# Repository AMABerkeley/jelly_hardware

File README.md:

# jelly_hardware
Hardware for Jelly Robot

More to come...

Useful for protecting against sparks and having an isolated ground for a computer.

Input Voltage is 24V from this device: [Kobalt](https://www.lowes.com/pd/Kobalt-24-Volt-1-5-Amp-Hours-Lithium-Power-Tool-Battery/1000090833)

Output Voltage at XT30 and XT60 is 24V

Output Voltage at Isolated pins: 5V 5A

V1.0 has been sent out.

TODO V2.0: Add PMOS to 24V to prevent damage to circuit if battery connected wrong way. Add connector for computer power. Add LED indicators.

Components:

DCDC Isolated 5V5A
https://www.digikey.com/product-detail/en/traco-power/THL-25-2411/1951-1620-ND/9382657
https://www.tracopower.com/products/thl25.pdf
https://assets.tracopower.com/20190412132953/THL25/documents/thl25-application.pdf

Inductor
https://www.mouser.com/ProductDetail/Coilcraft/XEL6060-222MEB?qs=sGAEpiMZZMsg%252By3WlYCkU1c2wN3ttFq7viHBlk82CxY%3D

NMOS
current nmos https://www.digikey.com/product-detail/en/stmicroelectronics/STP160N3LL/497-16021-5-ND/5455754
backup NMOS https://www.digikey.com/product-detail/en/infineon-technologies/IRLB3813PBF/IRLB3813PBF-ND/2118485

Batttery Terminal Connector
https://www.digikey.com/product-detail/en/te-connectivity-amp-connectors/1-725996-2/A130982-ND/2055902
Specs https://www.te.com/commerce/DocumentDelivery/DDEController?Action=showdoc&DocId=Catalog+Section%7F82004_FASTON_PCB_Tabs_Receptacles%7F0914%7Fpdf%7FEnglish%7FENG_CS_82004_FASTON_PCB_Tabs_Receptacles_0914.pdf%7F725996-2

Inspiration: https://easyeda.com/editor#id=83191bc7c7a1436bab31f7c8314d08c5|0a66ceef99064df6ad66a18129efbc26

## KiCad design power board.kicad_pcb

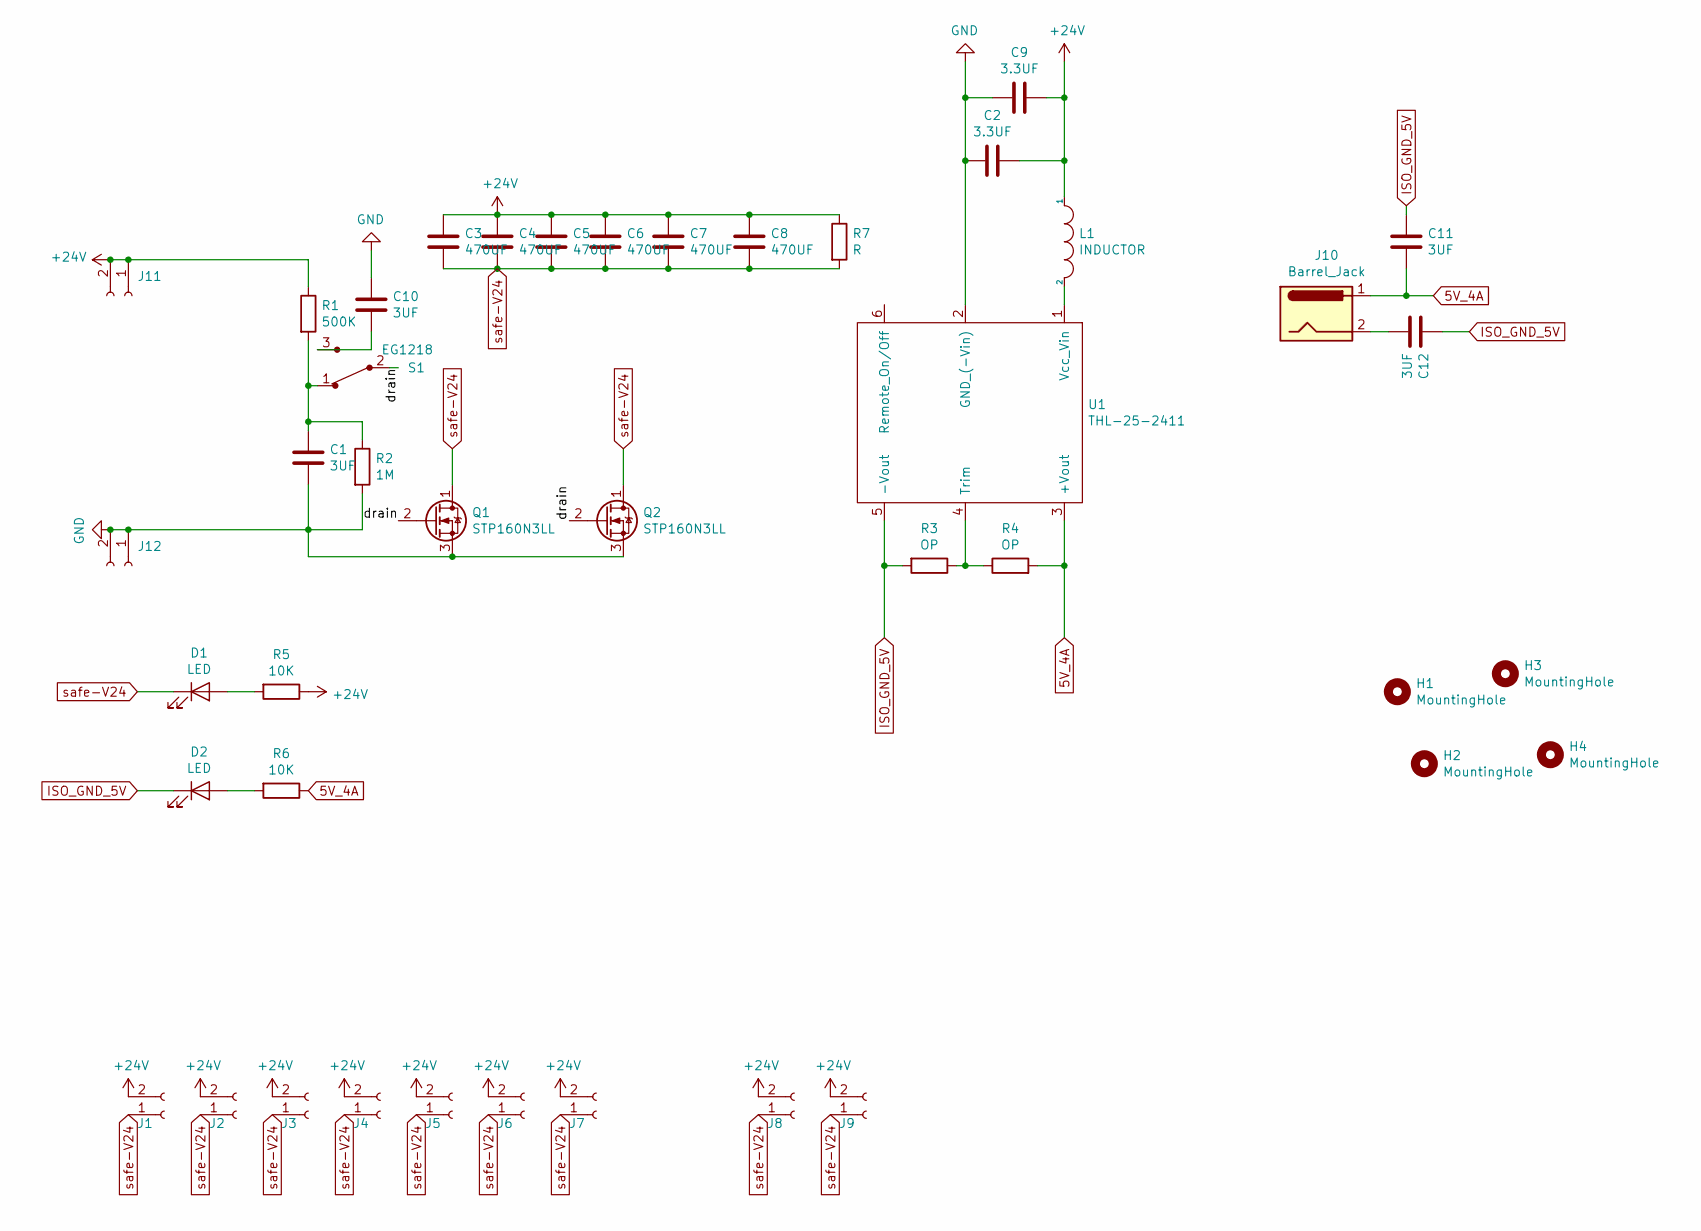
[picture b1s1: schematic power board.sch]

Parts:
C1, C10, C11, C12: 3UF; C_0805_2012Metric_Pad1.15x1.40mm_HandSolder
C2, C9: 3.3UF; C_0805_2012Metric_Pad1.15x1.40mm_HandSolder
C3, C4, C5, C6, C7, C8: 470UF; CP_Radial_D10.0mm_P5.00mm
D1, D2: LED; LED_0603_1608Metric_Pad1.05x0.95mm_HandSolder
H1, H2, H3, H4: MountingHole; MountingHole_3.2mm_M3_Pad_Via
J1, J2, J3, J4, J5, J6, J7: Conn_01x02_Female; AMASS_XT30U-F_1x02_P5.0mm_Vertical
J8, J9: Conn_01x02_Female; XT-60_female
J10: Barrel_Jack; BarrelJack_CUI_PJ-063AH_Horizontal
J11, J12: Conn_01x02_Female; battery_conector_powerpack
L1: INDUCTOR; XEL6060-152MEC
Q1, Q2: STP160N3LL; MOSFET_Down
R1: 500K; R_0805_2012Metric_Pad1.15x1.40mm_HandSolder
R2: 1M; R_0805_2012Metric_Pad1.15x1.40mm_HandSolder
R3, R4: OP; R_0805_2012Metric_Pad1.15x1.40mm_HandSolder
R5, R6: 10K; R_0805_2012Metric_Pad1.15x1.40mm_HandSolder
R7: R; R_0805_2012Metric_Pad1.15x1.40mm_HandSolder
S1: EG1218; Switch_Slide_11.6x4mm_EG1218; MPN EG1218; Digi-Key_PN EG1903-ND
U1: THL-25-2411; Converter_DCDC_TRACO_TEN20-xxxx_THT-modified

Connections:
5V_4A: C11.2, J10.1, R4.2, R6.1, U1.3 (+Vout)
+24V: C2.2, C3.1, C4.1, C5.1, C6.1, C7.1, C8.1, C9.2, J1.2, J2.2, J3.2, J4.2, J5.2, J6.2, J7.2, J8.2, J9.2, J11.1, J11.2, L1.1, R1.1, R5.1, R7.1
/drain: Q1.2 (G), Q2.2 (G), S1.2
GND: C1.2, C2.1, C9.1, C10.1, J12.1, J12.2, Q1.3 (S), Q2.3 (S), R2.2, U1.2 (GND_(-Vin))
ISO_GND_5V: C11.1, C12.1, D2.1 (K), R3.2, U1.5 (-Vout)
unnamed: C1.1, R1.2, R2.1, S1.1
unnamed: C10.2, S1.3
unnamed: C12.2, J10.2
unnamed: D1.2 (A), R5.2
unnamed: D2.2 (A), R6.2
unnamed: L1.2, U1.1 (Vcc_Vin)
unnamed: R3.1, R4.1, U1.4 (Trim)
safe-V24: C3.2, C4.2, C5.2, C6.2, C7.2, C8.2, D1.1 (K), J1.1, J2.1, J3.1, J4.1, J5.1, J6.1, J7.1, J8.1, J9.1, Q1.1 (D), Q2.1 (D), R7.2

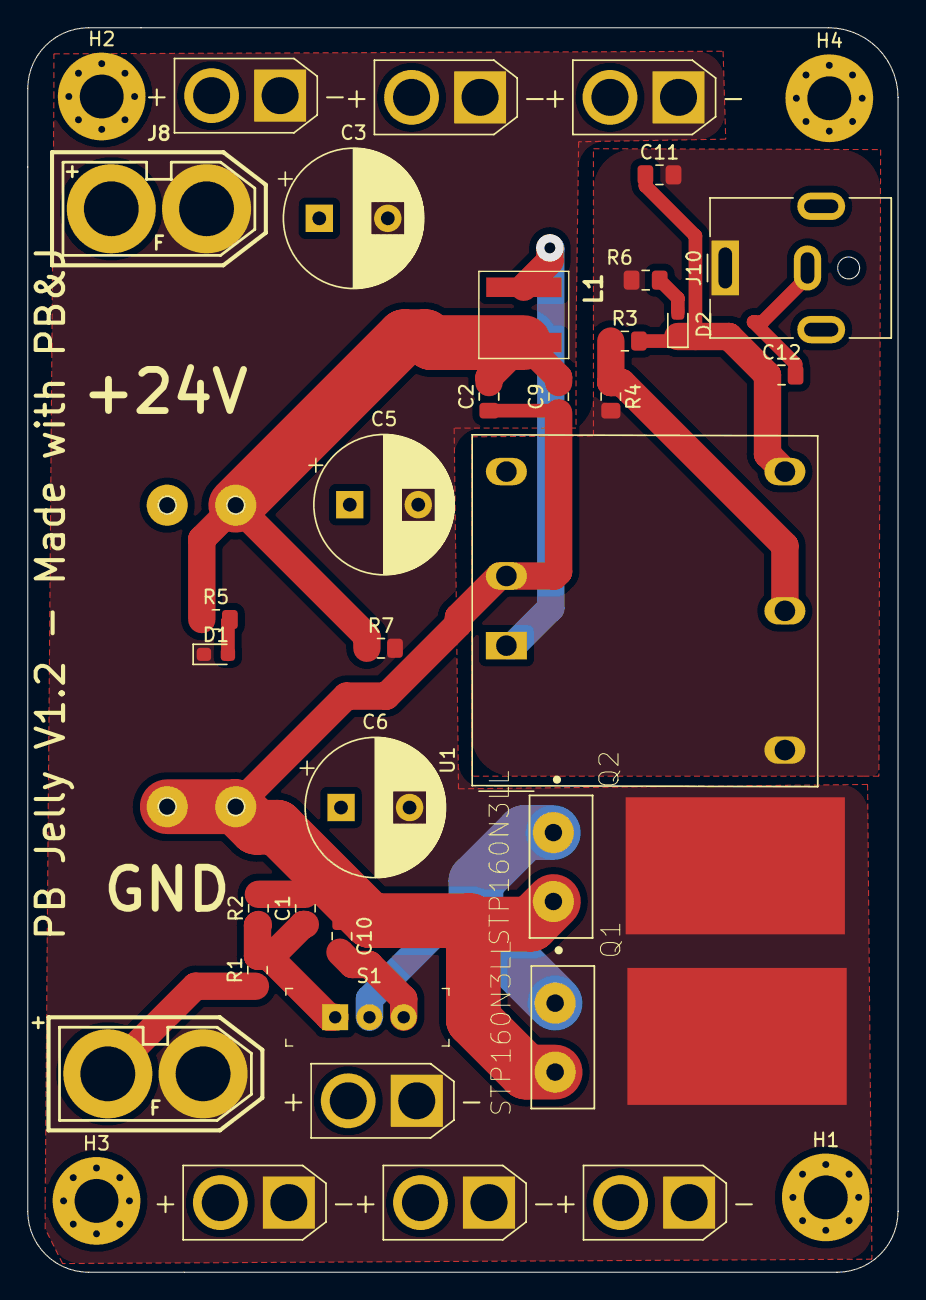
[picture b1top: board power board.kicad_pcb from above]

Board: 2 copper layers, 63.5 x 90.8 mm, 39 parts (0 on the bottom side), 13 nets.

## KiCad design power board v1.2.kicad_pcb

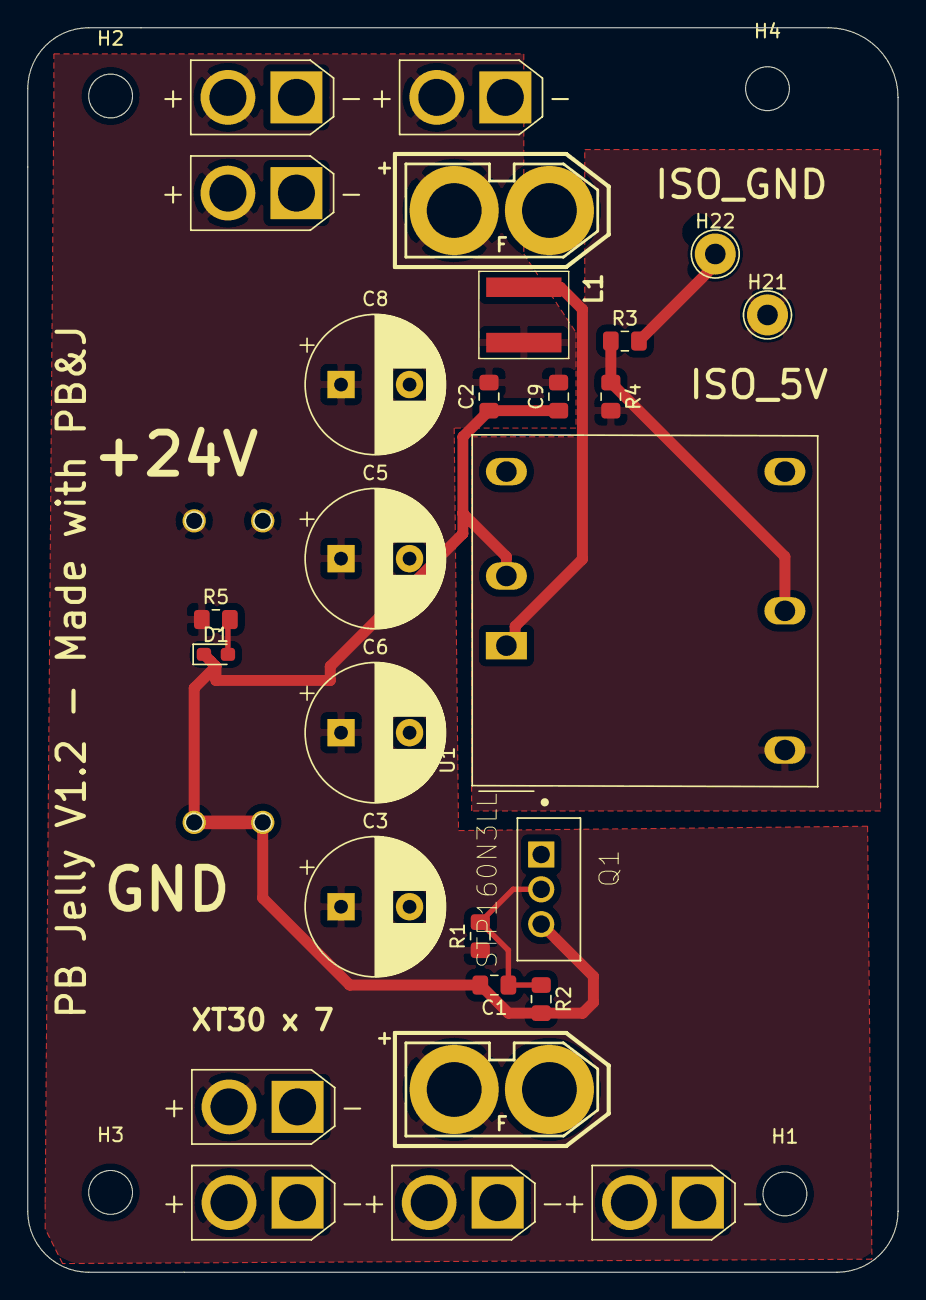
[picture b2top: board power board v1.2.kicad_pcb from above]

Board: 2 copper layers, 63.5 x 90.8 mm, 33 parts (0 on the bottom side), 9 nets.

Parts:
C1: .1UF; C_0805_2012Metric_Pad1.15x1.40mm_HandSolder
C2, C9: 3.3UF; C_0805_2012Metric_Pad1.15x1.40mm_HandSolder
C3, C5, C6, C8: 470UF; CP_Radial_D10.0mm_P5.00mm
D1: LED; LED_0603_1608Metric_Pad1.05x0.95mm_HandSolder
H1, H2, H3, H4: MountingHole; MountingHole_3.2mm_M3
H21, H22: MountingHole_Pad; TestPoint_THTPad_D3.0mm_Drill1.5mm
J1, J2, J3, J4, J5, J6, J7: Conn_01x02_Female; AMASS_XT30U-F_1x02_P5.0mm_Vertical
J9, J10: Conn_01x02_Female; XT-60_female
J11, J12: Conn_01x02_Female; battery_conector_powerpack
L1: INDUCTOR; XEL6060-152MEC
Q1: STP160N3LL; TO254P1040X460X1935-3
R1, R2: 1K; R_0805_2012Metric_Pad1.15x1.40mm_HandSolder
R3, R4: OP; R_0805_2012Metric_Pad1.15x1.40mm_HandSolder
R5: 10K; R_0805_2012Metric_Pad1.15x1.40mm_HandSolder
U1: THL-25-2411; Converter_DCDC_TRACO_TEN20-xxxx_THT-modified

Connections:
5V_4A: H21.1, R4.2, U1.3
+24V: C2.2, C3.1, C5.1, C6.1, C8.1, C9.2, J1.2, J2.2, J3.2, J4.2, J5.2, J6.2, J7.2, J9.2, J10.2, J11.1, J11.2, L1.1, R1.1, R5.1
GND: C1.2, C2.1, C9.1, D1.1, J12.1, J12.2, Q1.3, R2.2, U1.2
ISO_GND_5V: H22.1, R3.2, U1.5
unnamed: C1.1, Q1.2, R1.2, R2.1
unnamed: D1.2, R5.2
unnamed: L1.2, U1.1
unnamed: R3.1, R4.1, U1.4
safe-V24: C3.2, C5.2, C6.2, C8.2, J1.1, J2.1, J3.1, J4.1, J5.1, J6.1, J7.1, J9.1, J10.1, Q1.1

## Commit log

2019-04-17 created initial v0.0 of board
2019-04-17 added photos
2019-04-17 deleted diode and added caps
2019-04-17 final V1.0 sent out -gerbers zipped
2019-04-18 need to add LED's
2019-04-26 added leds annd switch and decreased size
2019-04-29 added some nicer features
2019-05-12 updated board to v1.2
2019-05-12 added nicer pic
